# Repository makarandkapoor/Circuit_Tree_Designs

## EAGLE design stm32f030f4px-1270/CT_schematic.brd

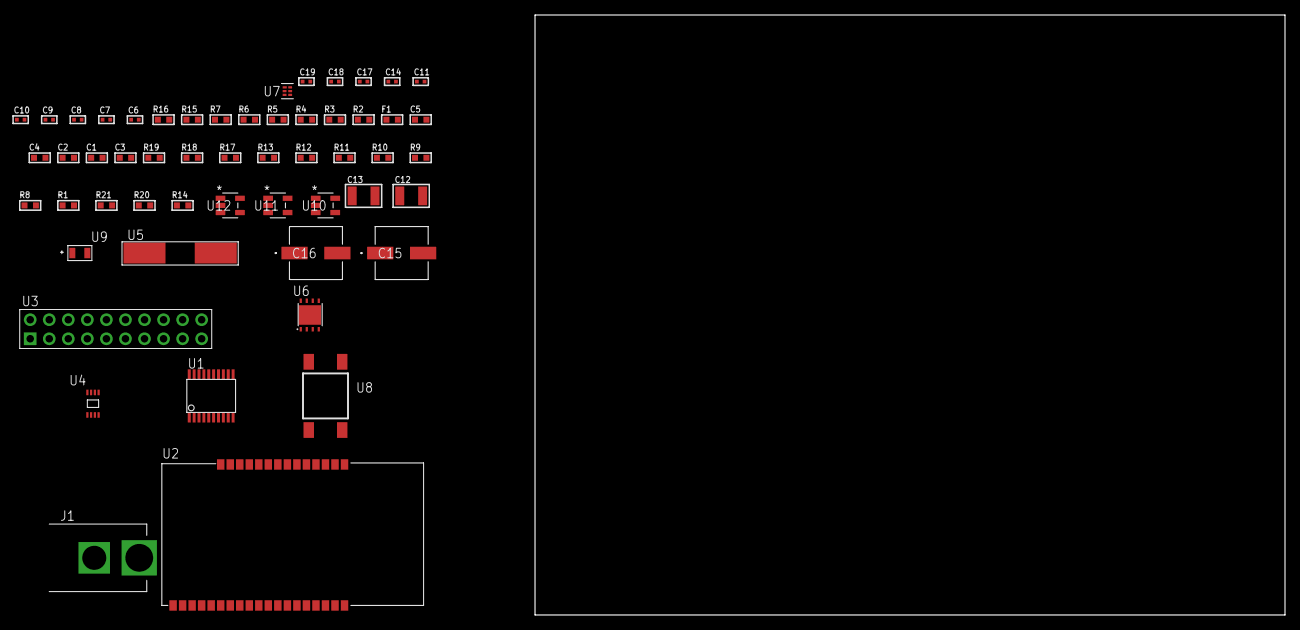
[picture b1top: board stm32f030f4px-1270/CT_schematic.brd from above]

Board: 2 copper layers, 100.0 x 80.0 mm, 54 parts (0 on the bottom side), 31 nets, no tracks yet.

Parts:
C1, C2: 1e-07; C0603
C3: 4.7e-06; C0603
C4: 1e-08; C0603
C5: 1e-06; C0603
C6, C7: 1e-11; C0402
C8, C9, C14: 1e-07; C0402
C10, C11, C17, C18, C19: 1e-08; C0402
C12, C13: 1e-05; C1210
C15, C16: 0.0001; EXV-9H
F1: 240.0; L0603
J1: PJ-037B; PJ-037B_PACKAGE
R1, R8, R9, R10, R11, R12, R13, R17, R18: 10000.0; R0603
R2, R16: 1000.0; R0603
R3: 1270.0; R0603
R4, R5: 4700.0; R0603
R6, R7: 2200.0; R0603
R14: 100000.0; R0603
R15: 1500.0; R0603
R19: 18000.0; R0603
R20: 470000.0; R0603
R21: 120000.0; R0603
U1: STM32F030F4P6; TSSOP20-I
U2: ETRX3587
U3: TST-110-05-T-D-RA
U4: 24AA128T-I/MNY; TDFN-8/6MM
U5: ABLS-25.000MHZ-B2F-T
U6: LP3878SDX-ADJ/NOPB; WSON-8
U7: TPS3895ADRYR; SON-6
U8: 4-1437565-2; SW_4-1437565-2
U9: Q65110A2395; LGM67K-G1J2-24-Z
U10, U11, U12: nc7sz125m5x; NC7SZ125M5X

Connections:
CLK_CRYSTAL_U1_2: C6.1, U1.2, U5.1
CLK_CRYSTAL_U1_3: C7.1, U1.3, U5.2
GND: C1.2, C2.2, C3.2, C4.2, C5.2, C6.2, C7.2, C8.2, C9.2, C10.2, C11.2, C12.2, C13.2, C14.2, C15.2, C16.2, C17.2, C18.2, C19.2, J1.2, R2.2, R8.2, R9.2, R16.2, R19.2, R21.2, U1.15, U2.1, U2.13, U2.19, U2.20, U2.31, U2.33, U3.4, U3.6, U3.8, U3.10, U3.12, U3.14, U3.16, U3.18, U3.20, U4.4, U4.7, U6.3, U6.PAD, U7.2, U9.C, U10.2, U10.3, U11.1, U11.3, U12.1, U12.3
NET_U1_1: R8.1, U1.1
NET_U1_4: R5.1, U1.4, U12.4
NET_U1_5: C4.1, C5.1, F1.1, U1.5
NET_U1_13: R3.1, U1.13, U9.A
NET_U1_14: R1.1, U1.14, U8.3, U8.4
NET_U1_17: R6.1, U1.17, U4.6
NET_U1_18: R7.1, U1.18, U4.5
NET_U2_7: R4.1, U2.7, U11.4
NET_U2_21: R9.1, U2.21
NET_U4_1: R11.1, U4.1
NET_U4_2: R12.1, U4.2
NET_U4_3: R13.1, U4.3
NET_U6_1: C11.1, U6.1
NET_U6_6: R15.2, R16.1, U6.6
NET_U6_8: R14.1, U6.8
NET_U7_1: R18.1, R19.1, U7.1
NET_U7_3: R20.2, R21.1, U7.3
NET_U7_4: R17.1, U7.4, U10.4, U11.2, U12.2
NET_U8_1: R2.1, U8.1, U8.2
PROC_SYS_SWCLK: U1.20, U3.9
PROC_SYS_SWDIO: U1.19, U3.7
PROC_USART1_CTS: U1.6, U2.8
PROC_USART1_RTS: U1.7, U2.6
PROC_USART1_RX: U1.9, U2.17
PROC_USART1_TX: U1.8, U2.18
RST_OUT_U3_SRESET_B: R10.1, U3.15, U10.1
VCC_S1_16V0: C12.1, C15.1, C16.1, J1.1, R14.2, U6.4
VCC_TIER1_2V5: C1.1, C2.1, C3.1, C8.1, C9.1, C10.1, C13.1, C14.1, C17.1, C18.1, C19.1, F1.2, R1.2, R3.2, R4.2, R5.2, R6.2, R7.2, R10.2, R11.2, R12.2, R13.2, R15.1, R17.2, R18.2, R20.1, U1.16, U2.32, U3.1, U4.8, U6.5, U7.6, U10.5, U11.5, U12.5

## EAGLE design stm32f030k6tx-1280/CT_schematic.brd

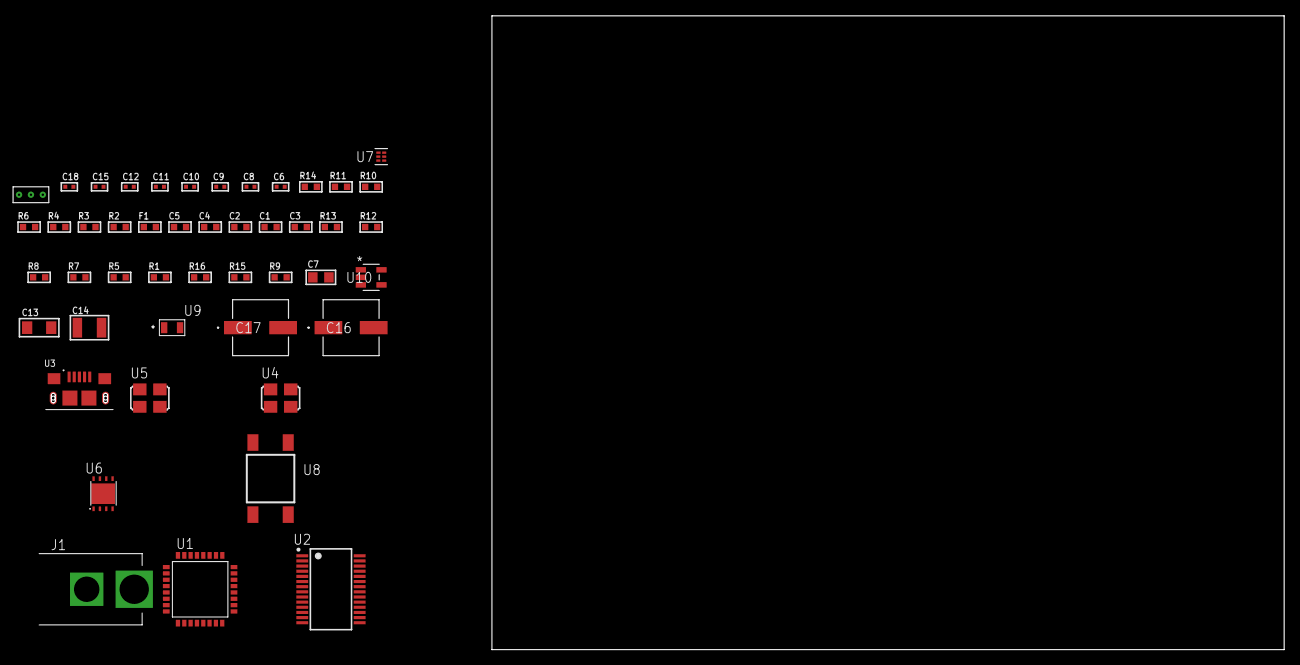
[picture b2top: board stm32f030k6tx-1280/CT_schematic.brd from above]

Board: 2 copper layers, 155.6 x 80.0 mm, 47 parts (0 on the bottom side), 29 nets, no tracks yet.

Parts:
C1, C2: 1e-07; C0603
C3: 4.7e-06; C0603
C4: 1e-08; C0603
C5: 1e-06; C0603
C6, C8, C9, C15: 1e-07; C0402
C7: 4.7e-06; C0805
C10, C11, C12, C18: 1e-08; C0402
C13: 1e-05; C1206
C14: 1e-05; C1210
C16, C17: 0.0001; EXV-9H
F1: 240.0; L0603
J1: PJ-037B; PJ-037B_PACKAGE
R1, R5, R7, R8, R12, R13: 10000.0; R0603
R2, R11: 1000.0; R0603
R3: 1600.5; R0603
R4, R6: 4700.0; R0603
R9: 100000.0; R0603
R10: 2231.0; R0603
R14: 9100.0; R0603
R15: 680000.0; R0603
R16: 120000.0; R0603
U1: STM32F030K6T6; LQFP32
U2: FT232RL-REEL; SSOP-28
U3: 10118193-0001LF; FCI_10118193-0001LF
U4: ASFL1-12MHZ-NCS; ASFL1
U5: ASFL1-25MHZ-NCS; ASFL1
U6: LP3878SDX-ADJ/NOPB; WSON-8
U7: TPS3895ADRYR; SON-6
U8: 4-1437565-2; SW_4-1437565-2
U9: Q65110A2395; LGM67K-G1J2-24-Z
U10: nc7sz125m5x; NC7SZ125M5X
U11: Dummy; DUMMY_PACKAGE_99

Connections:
CLK_U1_2: U1.2, U5.3
CLK_U2_27: U2.27, U4.3
GND: C1.2, C2.2, C3.2, C4.2, C5.2, C6.2, C7.2, C8.2, C9.2, C10.2, C11.2, C12.2, C13.2, C14.2, C15.2, C16.2, C17.2, C18.2, J1.2, R2.2, R5.2, R8.2, R11.2, R14.2, R16.2, U1.16, U1.32, U2.7, U2.18, U2.21, U2.25, U2.26, U3.5, U3.6, U3.7, U3.8, U3.9, U4.2, U5.2, U6.3, U6.PAD, U7.2, U9.C, U10.1, U10.3, U11.1
NET_U1_4: R4.1, U1.4, U10.4
NET_U1_5: C4.1, C5.1, F1.1, U1.5
NET_U1_29: R3.1, U1.29, U9.A
NET_U1_30: R1.1, U1.30, U8.3, U8.4
NET_U1_31: R5.1, U1.31
NET_U2_14: R7.1, U2.14
NET_U2_17: C8.1, U2.17
NET_U2_19: R8.1, U2.19
NET_U3_1: R6.1, U3.1
NET_U3_2: U2.16, U3.2
NET_U3_3: U2.15, U3.3
NET_U6_1: C12.1, U6.1
NET_U6_6: R10.2, R11.1, U6.6
NET_U6_8: R9.1, U6.8
NET_U7_1: R13.1, R14.1, U7.1
NET_U7_3: R15.2, R16.1, U7.3
NET_U7_4: R12.1, U7.4, U10.2
NET_U8_1: R2.1, U8.1, U8.2
PROC_TIM1_CH3N: U1.15, U11.3
PROC_TIM1_CH4: U1.21, U11.2
PROC_USART1_CTS: U1.6, U2.3
PROC_USART1_RTS: U1.7, U2.11
PROC_USART1_RX: U1.9, U2.1
PROC_USART1_TX: U1.8, U2.5
VCC_S1_6V0: C13.1, C16.1, C17.1, J1.1, R9.2, U6.4
VCC_TIER1_3V3: C1.1, C2.1, C3.1, C6.1, C7.1, C9.1, C10.1, C11.1, C14.1, C15.1, C18.1, F1.2, R1.2, R3.2, R4.2, R7.2, R10.1, R12.2, R13.2, R15.1, U1.1, U1.17, U2.4, U2.20, U4.4, U5.4, U6.5, U7.6, U10.5

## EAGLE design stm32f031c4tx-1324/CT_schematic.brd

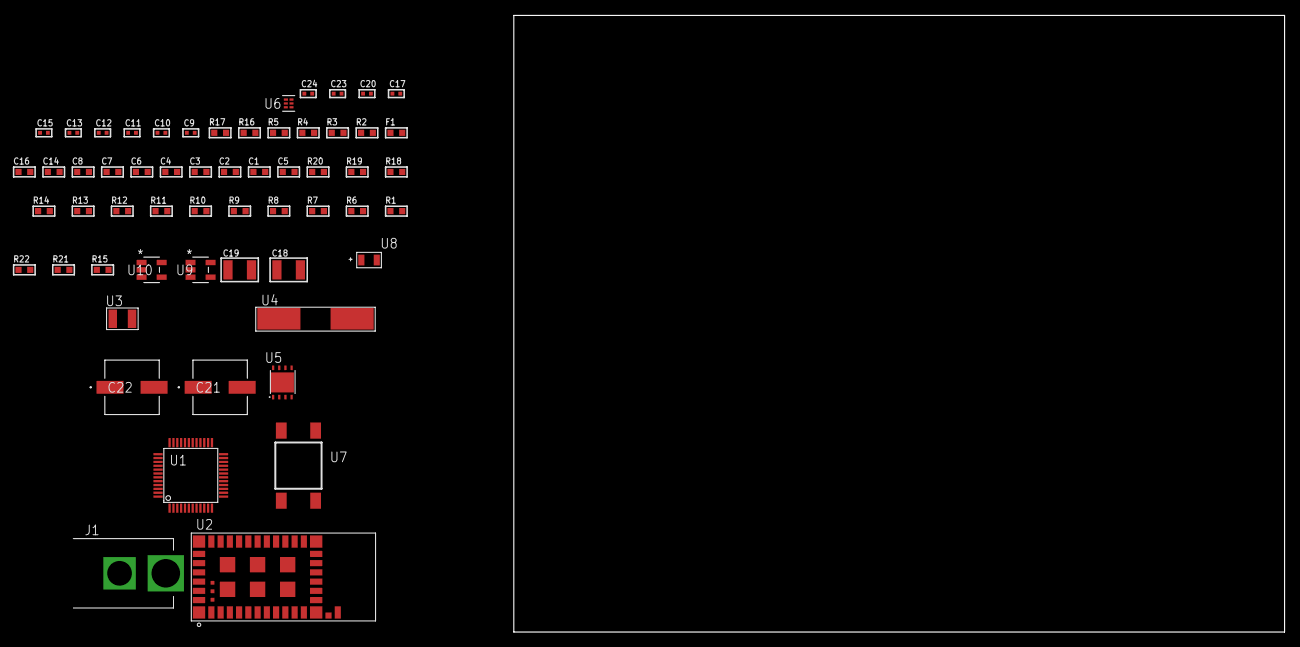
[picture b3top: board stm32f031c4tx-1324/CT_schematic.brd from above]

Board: 2 copper layers, 100.0 x 80.0 mm, 58 parts (0 on the bottom side), 28 nets, no tracks yet.

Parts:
C1, C8, C14, C16: 1e-06; C0603
C2, C3, C4, C6: 1e-07; C0603
C5: 4.7e-06; C0603
C7: 1e-08; C0603
C9, C10, C11, C12: 1e-11; C0402
C13, C15, C20: 1e-07; C0402
C17, C23, C24: 1e-08; C0402
C18, C19: 1e-05; C1210
C21, C22: 0.0001; EXV-9H
F1: 240.0; L0603
J1: PJ-037B; PJ-037B_PACKAGE
R1, R6, R7, R14, R18, R19: 10000.0; R0603
R2, R17: 1000.0; R0603
R3: 1500.0; R0603
R4, R5: 4700.0; R0603
R8, R9, R10, R11, R12, R13: 34000.0; R0603
R15: 100000.0; R0603
R16: 2000.0; R0603
R20: 11000.0; R0603
R21: 620000.0; R0603
R22: 120000.0; R0603
U1: stm32f031c4t7; LQFP48
U2: 88-00153-02
U3: ABS07-32.768KHZ-7-T
U4: ABLS-25.000MHZ-B2F-T
U5: LP3878SDX-ADJ/NOPB; WSON-8
U6: TPS3895ADRYR; SON-6
U7: 4-1437565-2; SW_4-1437565-2
U8: Q65110A2395; LGM67K-G1J2-24-Z
U9, U10: nc7sz125m5x; NC7SZ125M5X

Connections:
CLK_CRYSTAL_U1_3: C9.1, U1.3, U3.1
CLK_CRYSTAL_U1_4: C10.1, U1.4, U3.2
CLK_CRYSTAL_U1_5: C11.1, U1.5, U4.1
CLK_CRYSTAL_U1_6: C12.1, U1.6, U4.2
GND: C1.2, C2.2, C3.2, C4.2, C5.2, C6.2, C7.2, C8.2, C9.2, C10.2, C11.2, C12.2, C13.2, C14.2, C15.2, C16.2, C17.2, C18.2, C19.2, C20.2, C21.2, C22.2, C23.2, C24.2, J1.2, R2.2, R6.2, R17.2, R20.2, R22.2, U1.8, U1.23, U1.47, U2.1, U2.9, U2.13, U2.14, U2.15, U2.16, U2.17, U2.18, U2.19, U2.20, U2.21, U2.22, U2.23, U2.24, U2.25, U2.26, U2.27, U2.31, U2.32, U2.39, U2.40, U2.41, U2.42, U2.43, U2.44, U2.49, U5.3, U5.PAD, U6.2, U8.C, U9.1, U9.3, U10.1, U10.3
NET_U1_7: R5.1, U1.7, U10.4
NET_U1_9: C7.1, C8.1, F1.1, U1.9
NET_U1_44: R6.1, U1.44
NET_U1_45: R3.1, U1.45, U8.A
NET_U1_46: R1.1, U1.46, U7.3, U7.4
NET_U2_2: R10.1, U2.2
NET_U2_6: R14.1, U2.6
NET_U2_10: R4.1, U2.10, U9.4
NET_U2_11: R7.1, U2.11
NET_U2_34: R9.1, U2.34
NET_U5_1: C17.1, U5.1
NET_U5_6: R16.2, R17.1, U5.6
NET_U5_8: R15.1, U5.8
NET_U6_1: R19.1, R20.1, U6.1
NET_U6_3: R21.2, R22.1, U6.3
NET_U6_4: R18.1, U6.4, U9.2, U10.2
NET_U7_1: R2.1, U7.1, U7.2
PROC_SPI1_MISO: R8.1, U1.16, U2.35
PROC_SPI1_MOSI: R12.1, U1.17, U2.37
PROC_SPI1_NSS: R11.1, U1.14, U2.38
PROC_SPI1_SCK: R13.1, U1.15, U2.36
VCC_S1_11V3: C18.1, C21.1, C22.1, J1.1, R15.2, U5.4
VCC_TIER1_3V0: C1.1, C2.1, C3.1, C4.1, C5.1, C6.1, C13.1, C14.1, C15.1, C16.1, C19.1, C20.1, C23.1, C24.1, F1.2, R1.2, R3.2, R4.2, R5.2, R7.2, R8.2, R9.2, R10.2, R11.2, R12.2, R13.2, R14.2, R16.1, R18.2, R19.2, R21.1, U1.1, U1.24, U1.48, U2.12, U2.33, U5.5, U6.6, U9.5, U10.5

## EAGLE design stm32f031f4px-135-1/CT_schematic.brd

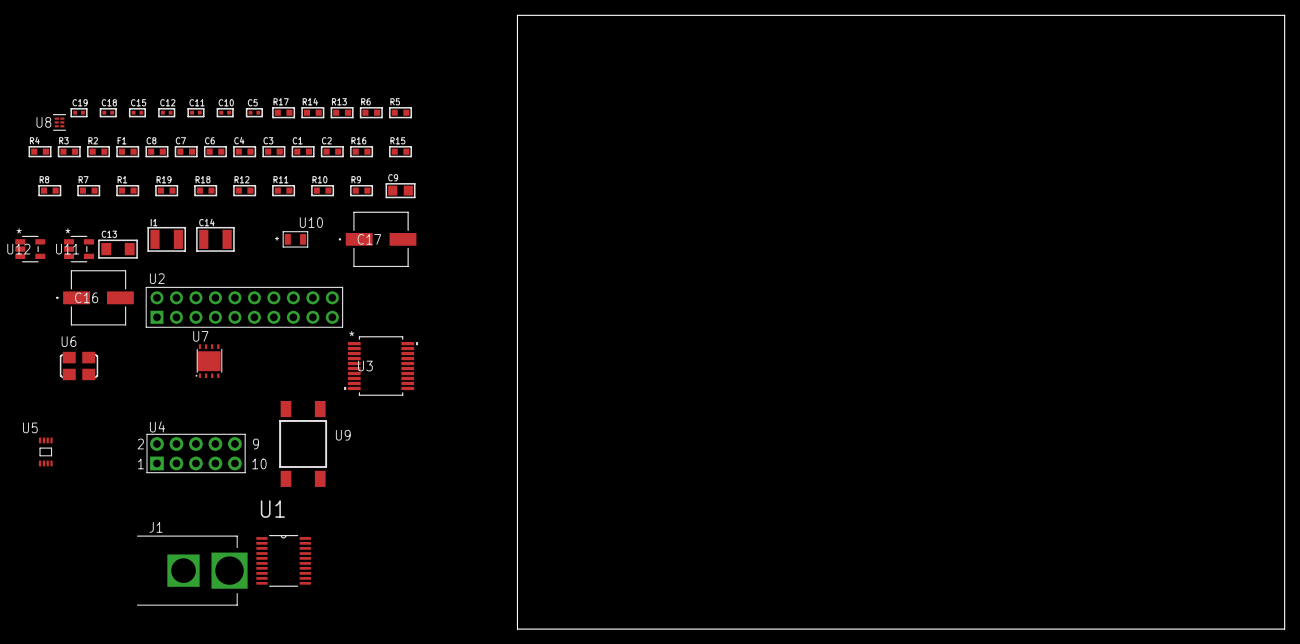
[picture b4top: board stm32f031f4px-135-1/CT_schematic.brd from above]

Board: 2 copper layers, 100.0 x 80.0 mm, 53 parts (0 on the bottom side), 37 nets, no tracks yet.

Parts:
C1: 1e-07; C0603
C2: 4.7e-06; C0603
C3: 1e-08; C0603
C4, C6, C7, C8: 1e-06; C0603
C5, C15: 1e-07; C0402
C9: 4.7e-06; C0805
C10, C11, C12, C18, C19: 1e-08; C0402
C13: 1e-05; C1206
C14: 1e-05; C1210
C16, C17: 0.0001; EXV-9H
F1: 240.0; L0603
I1: 1.5e-05; L1210
J1: PJ-037B; PJ-037B_PACKAGE
R1, R7, R8, R15, R16: 10000.0; R0603
R2, R14: 1000.0; R0603
R3: 1600.5; R0603
R4: 4700.0; R0603
R5, R6: 2200.0; R0603
R9, R10, R11, R12: 100000.0; R0603
R13: 2231.0; R0603
R17: 9100.0; R0603
R18: 680000.0; R0603
R19: 120000.0; R0603
U1: stm32f031f4p7; TSSOP20
U2: TST-110-05-T-D-RA
U3: MAX3218EAP+T; SSOP-20
U4: HTSS-105-01-G-D
U5: 24AA01T-I/MNY; TDFN-8/6MM
U6: ASFL1-25MHZ-NCS; ASFL1
U7: LP3878SDX-ADJ/NOPB; WSON-8
U8: TPS3895ADRYR; SON-6
U9: 4-1437565-2; SW_4-1437565-2
U10: Q65110A2395; LGM67K-G1J2-24-Z
U11, U12: nc7sz125m5x; NC7SZ125M5X

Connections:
CLK_U1_2: U1.2, U6.3
GND: C1.2, C2.2, C3.2, C4.2, C5.2, C6.2, C7.2, C8.2, C10.2, C11.2, C12.2, C13.2, C14.2, C15.2, C16.2, C17.2, C18.2, C19.2, J1.2, R2.2, R7.2, R14.2, R17.2, R19.2, U1.15, U2.4, U2.6, U2.8, U2.10, U2.12, U2.14, U2.16, U2.18, U2.20, U3.5, U3.17, U3.20, U4.9, U5.4, U6.2, U7.3, U7.PAD, U8.2, U10.C, U11.2, U11.3, U12.1, U12.3
NET_U1_1: R7.1, U1.1
NET_U1_4: R4.1, U1.4, U12.4
NET_U1_5: C3.1, C4.1, F1.1, U1.5
NET_U1_13: R3.1, U1.13, U10.A
NET_U1_14: R1.1, U1.14, U9.3, U9.4
NET_U1_17: R5.1, U1.17, U5.6
NET_U1_18: R6.1, U1.18, U5.5
NET_U3_1: I1.1, U3.1
NET_U3_2: R9.1, U3.2
NET_U3_3: R10.1, U3.3
NET_U3_4: R11.1, U3.4
NET_U3_15: C8.1, U3.15
NET_U3_16: C9.2, U3.16
NET_U3_18: C9.1, U3.18
NET_U3_19: C7.1, U3.19
NET_U4_3: U3.12, U4.3
NET_U4_4: U3.11, U4.4
NET_U4_5: U3.14, U4.5
NET_U4_6: U3.13, U4.6
NET_U7_1: C12.1, U7.1
NET_U7_6: R13.2, R14.1, U7.6
NET_U7_8: R12.1, U7.8
NET_U8_1: R16.1, R17.1, U8.1
NET_U8_3: R18.2, R19.1, U8.3
NET_U8_4: R15.1, U8.4, U11.4, U12.2
NET_U9_1: R2.1, U9.1, U9.2
PROC_SYS_SWCLK: U1.20, U2.9
PROC_SYS_SWDIO: U1.19, U2.7
PROC_USART1_CTS: U1.6, U3.8
PROC_USART1_RTS: U1.7, U3.10
PROC_USART1_RX: U1.9, U3.9
PROC_USART1_TX: U1.8, U3.7
RST_OUT_U2_SRESET_B: R8.1, U2.15, U11.1
VCC_S1_6V0: C13.1, C16.1, C17.1, J1.1, R12.2, U7.4
VCC_TIER1_3V3: C1.1, C2.1, C5.1, C6.1, C10.1, C11.1, C14.1, C15.1, C18.1, C19.1, F1.2, I1.2, R1.2, R3.2, R4.2, R5.2, R6.2, R8.2, R9.2, R10.2, R11.2, R13.1, R15.2, R16.2, R18.1, U1.16, U2.1, U3.6, U5.7, U5.8, U6.4, U7.5, U8.6, U11.5, U12.5

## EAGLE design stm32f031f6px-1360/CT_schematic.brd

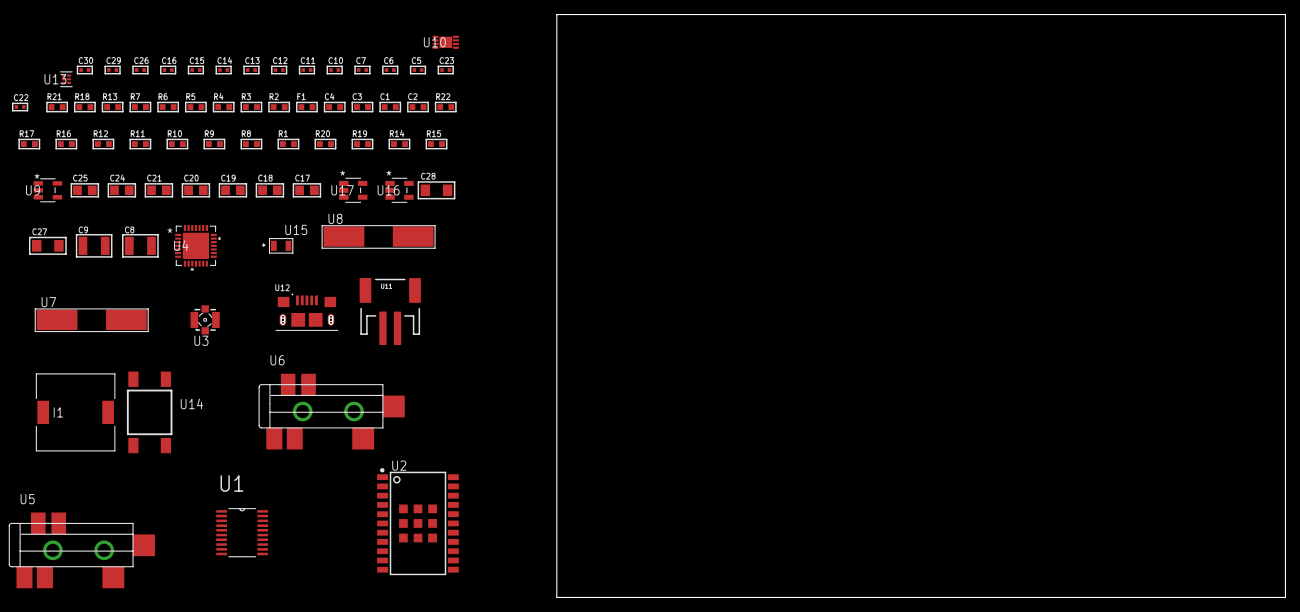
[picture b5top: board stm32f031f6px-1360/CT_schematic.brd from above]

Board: 2 copper layers, 71 parts (0 on the bottom side), 36 nets, no tracks yet.

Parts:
C1: 1e-07; C0603
C2: 4.7e-06; C0603
C3: 1e-08; C0603
C4: 1e-06; C0603
C5, C6: 1e-11; C0402
C7, C12, C13, C14, C15, C16, C26: 1e-07; C0402
C8, C9: 2.2e-05; C1210
C10, C11: 1e-09; C0402
C17, C18, C19, C20, C21, C24, C25: 1e-05; C0805
C22, C23: 2.2e-11; C0402
C27, C28: 1e-05; C1206
C29, C30: 1e-08; C0402
F1: 240.0; L0603
I1: 2.5e-06; DR1040
R1, R8, R9, R16, R17, R22: 10000.0; R0603
R2: 1000.0; R0603
R3: 1600.5; R0603
R4, R5: 4700.0; R0603
R6, R7: 2200.0; R0603
R10, R11, R12: 47000.0; R0603
R13: 680.0; R0603
R14: 220000.0; R0603
R15: 1000000.0; R0603
R18: 9100.0; R0603
R19: 680000.0; R0603
R20: 120000.0; R0603
R21: 2000.0; R0603
U1: stm32f031f6p7; TSSOP20
U2: A2200-A
U3: 73412-0114; COAXIAL_C
U4: WM8731CLSEFL; QFN-28
U5, U6: SJ-43515TS-SMT-TR
U7: ABLS-25.000MHZ-B2F-T
U8: ABLS-12.288MHZ-B4-T
U9: ltc3406es5; TSOT-23-5
U10: MCP73831T-2ACI/MC; DFN8_2X3MC
U11: S2B-PH-SM4-TB(LF)(SN); JST-2-SMD
U12: 10118193-0001LF; FCI_10118193-0001LF
U13: TPS3895ADRYR; SON-6
U14: 4-1437565-2; SW_4-1437565-2
U15: Q65110A2395; LGM67K-G1J2-24-Z
U16, U17: nc7sz125m5x; NC7SZ125M5X

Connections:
CLK_CRYSTAL_U1_2: C5.1, U1.2, U7.1
CLK_CRYSTAL_U1_3: C6.1, U1.3, U7.2
CLK_CRYSTAL_U4_1: C22.1, U4.1, U8.1
CLK_CRYSTAL_U4_2: C23.1, U4.2, U8.2
GND: C1.2, C2.2, C3.2, C4.2, C5.2, C6.2, C7.2, C11.2, C12.2, C13.2, C14.2, C15.2, C16.2, C17.2, C18.2, C19.2, C20.2, C21.2, C22.2, C23.2, C24.2, C25.1, C25.2, C26.2, C27.2, C28.2, C29.2, C30.2, R2.2, R8.2, R10.2, R11.2, R12.2, R14.2, R18.2, R20.2, R21.2, U1.15, U2.7, U2.8, U2.23, U2.24, U2.25, U2.26, U2.27, U2.28, U2.29, U2.30, U2.31, U4.4, U4.15, U4.19, U4.25, U4.26, U4.29, U5.1, U6.1, U9.2, U10.6, U10.9, U11.2, U12.5, U12.6, U12.7, U12.8, U12.9, U13.2, U15.C, U16.1, U16.3, U17.1, U17.3
INPUT_USBPOWER_5V: C27.1, R22.2, U10.1, U10.2, U12.1
NET_U1_1: R8.1, U1.1
NET_U1_4: R5.1, U1.4, U17.4
NET_U1_5: C3.1, C4.1, F1.1, U1.5
NET_U1_17: R6.1, U1.17, U2.15
NET_U1_18: R7.1, U1.18, U2.16
NET_U1_19: R3.1, U1.19, U15.A
NET_U1_20: R1.1, U1.20, U14.3, U14.4
NET_U2_2: R9.2, U2.2
NET_U2_17: R9.1, U2.17
NET_U2_22: R4.1, U2.22, U16.4
NET_U3_1: U2.11, U3.1
NET_U3_2: U2.10, U3.2, U3.3, U3.4
NET_U4_20: C16.1, C21.1, U4.20
NET_U5_2: C9.1, R11.1, U5.2
NET_U5_5: C8.1, R10.1, U5.5
NET_U6_5: C10.1, C11.1, R12.1, R13.1, U6.5
NET_U9_3: I1.1, U9.3
NET_U9_5: R14.1, R15.1, U9.5
NET_U9_ATNET_3: I1.2, R15.2
NET_U10_5: R22.1, U10.5
NET_U10_8: R21.1, U10.8
NET_U13_1: R17.1, R18.1, U13.1
NET_U13_3: R19.2, R20.1, U13.3
NET_U13_4: R16.1, U13.4, U16.2, U17.2
NET_U14_1: R2.1, U14.1, U14.2
PROC_I2S1_CK: U1.11, U4.7
PROC_I2S1_SD: U1.13, U4.8
PROC_I2S1_WS: U1.10, U4.9, U4.11
VCC_S1_3V7: C24.1, C28.1, U9.4, U10.3, U10.4, U11.1
VCC_TIER1_3V3: C1.1, C2.1, C7.1, C12.1, C13.1, C14.1, C15.1, C17.1, C18.1, C19.1, C20.1, C25.2, C26.1, C29.1, C30.1, F1.2, I1.2, R1.2, R3.2, R4.2, R5.2, R6.2, R7.2, R15.2, R16.2, R17.2, R19.1, U1.16, U2.20, U4.3, U4.5, U4.12, U4.18, U13.6, U16.5, U17.5

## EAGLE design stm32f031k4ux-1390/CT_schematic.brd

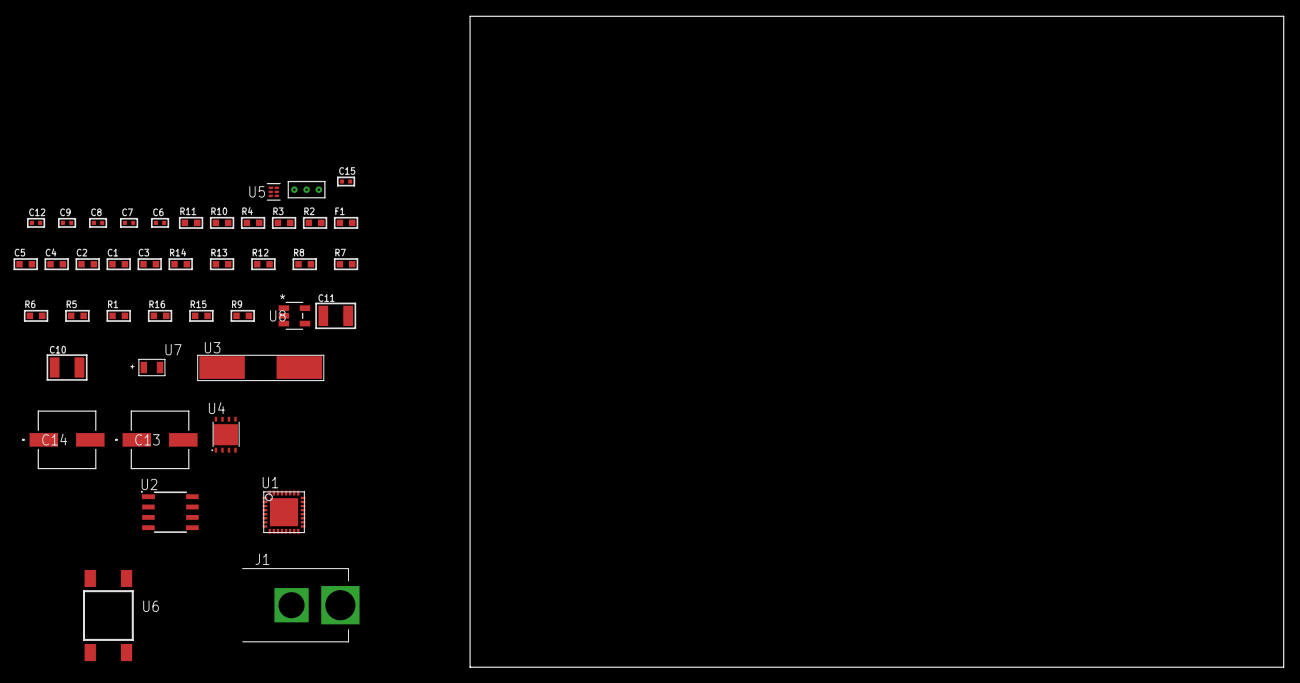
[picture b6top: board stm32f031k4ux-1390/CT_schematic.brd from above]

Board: 2 copper layers, 100.0 x 80.0 mm, 42 parts (0 on the bottom side), 25 nets, no tracks yet.

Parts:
C1, C2: 1e-07; C0603
C3: 4.7e-06; C0603
C4: 1e-08; C0603
C5: 1e-06; C0603
C6, C7: 1e-11; C0402
C8, C9, C15: 1e-08; C0402
C10, C11: 1e-05; C1210
C12: 1e-07; C0402
C13, C14: 0.0001; EXV-9H
F1: 240.0; L0603
J1: PJ-037B; PJ-037B_PACKAGE
R1, R5, R6, R7, R8, R12, R13: 10000.0; R0603
R2, R11: 1000.0; R0603
R3: 1270.0; R0603
R4: 4700.0; R0603
R9: 100000.0; R0603
R10: 1500.0; R0603
R14: 18000.0; R0603
R15: 470000.0; R0603
R16: 120000.0; R0603
U1: stm32f031k4u7; UFQFPN32
U2: AT25512N-SH-T; SOIC-8
U3: ABLS-25.000MHZ-B2F-T
U4: LP3878SDX-ADJ/NOPB; WSON-8
U5: TPS3895ADRYR; SON-6
U6: 4-1437565-2; SW_4-1437565-2
U7: Q65110A2395; LGM67K-G1J2-24-Z
U8: nc7sz125m5x; NC7SZ125M5X
U9: Dummy; DUMMY_PACKAGE_85

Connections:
CLK_CRYSTAL_U1_2: C6.1, U1.2, U3.1
CLK_CRYSTAL_U1_3: C7.1, U1.3, U3.2
GND: C1.2, C2.2, C3.2, C4.2, C5.2, C6.2, C7.2, C8.2, C9.2, C10.2, C11.2, C12.2, C13.2, C14.2, C15.2, J1.2, R2.2, R5.2, R11.2, R14.2, R16.2, U1.EPAD, U2.4, U4.3, U4.PAD, U5.2, U7.C, U8.1, U8.3, U9.1
NET_U1_4: R4.1, U1.4, U8.4
NET_U1_5: C4.1, C5.1, F1.1, U1.5
NET_U1_30: R3.1, U1.30, U7.A
NET_U1_31: R5.1, U1.31
NET_U1_32: R1.1, U1.32, U6.3, U6.4
NET_U2_3: R6.1, U2.3
NET_U2_7: R8.1, U2.7
NET_U4_1: C9.1, U4.1
NET_U4_6: R10.2, R11.1, U4.6
NET_U4_8: R9.1, U4.8
NET_U5_1: R13.1, R14.1, U5.1
NET_U5_3: R15.2, R16.1, U5.3
NET_U5_4: R12.1, U5.4, U8.2
NET_U6_1: R2.1, U6.1, U6.2
PROC_ADC_IN1: U1.7, U9.3
PROC_ADC_IN9: U1.15, U9.2
PROC_SPI1_MISO: U1.12, U2.2
PROC_SPI1_MOSI: U1.13, U2.5
PROC_SPI1_NSS: R7.1, U1.10, U2.1
PROC_SPI1_SCK: U1.11, U2.6
VCC_S1_15V0: C10.1, C13.1, C14.1, J1.1, R9.2, U4.4
VCC_TIER1_2V5: C1.1, C2.1, C3.1, C8.1, C11.1, C12.1, C15.1, F1.2, R1.2, R3.2, R4.2, R6.2, R7.2, R8.2, R10.1, R12.2, R13.2, R15.1, U1.1, U1.17, U2.8, U4.5, U5.6, U8.5

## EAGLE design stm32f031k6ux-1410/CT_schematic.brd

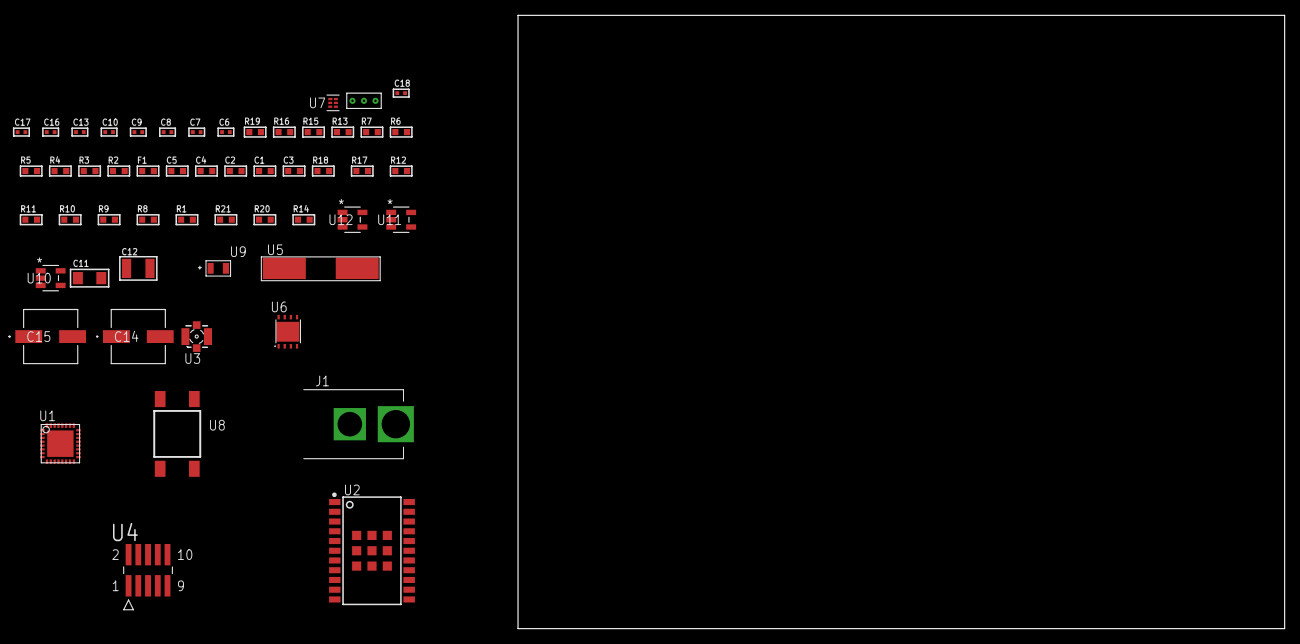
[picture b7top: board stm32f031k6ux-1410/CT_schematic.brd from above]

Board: 2 copper layers, 100.0 x 80.0 mm, 54 parts (0 on the bottom side), 30 nets, no tracks yet.

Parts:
C1, C2: 1e-07; C0603
C3: 4.7e-06; C0603
C4: 1e-08; C0603
C5: 1e-06; C0603
C6, C7: 1e-11; C0402
C8, C9, C13: 1e-07; C0402
C10, C16, C17, C18: 1e-08; C0402
C11: 1e-05; C1206
C12: 1e-05; C1210
C14, C15: 0.0001; EXV-9H
F1: 240.0; L0603
J1: PJ-037B; PJ-037B_PACKAGE
R1, R8, R9, R10, R11, R12, R17, R18: 10000.0; R0603
R2, R16: 1000.0; R0603
R3: 1600.5; R0603
R4, R5: 4700.0; R0603
R6, R7: 2200.0; R0603
R13: 5.0; R0603
R14: 100000.0; R0603
R15: 2231.0; R0603
R19: 9100.0; R0603
R20: 680000.0; R0603
R21: 120000.0; R0603
U1: stm32f031k6u7; UFQFPN32
U2: A2200-A
U3: 73412-0114; COAXIAL_C
U4: FTSH-105-01-L-DV-K; SAMTEC_FTSH-105-01-L-DV-K
U5: ABLS-25.000MHZ-B2F-T
U6: LP3878SDX-ADJ/NOPB; WSON-8
U7: TPS3895ADRYR; SON-6
U8: 4-1437565-2; SW_4-1437565-2
U9: Q65110A2395; LGM67K-G1J2-24-Z
U10, U11, U12: nc7sz125m5x; NC7SZ125M5X
U13: Dummy; DUMMY_PACKAGE_111

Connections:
CLK_CRYSTAL_U1_2: C6.1, U1.2, U5.1
CLK_CRYSTAL_U1_3: C7.1, U1.3, U5.2
GND: C1.2, C2.2, C3.2, C4.2, C5.2, C6.2, C7.2, C8.2, C9.2, C10.2, C11.2, C12.2, C13.2, C14.2, C15.2, C16.2, C17.2, C18.2, J1.2, R2.2, R8.2, R13.2, R16.2, R19.2, R21.2, U1.EPAD, U2.7, U2.8, U2.23, U2.24, U2.25, U2.26, U2.27, U2.28, U2.29, U2.30, U2.31, U4.3, U4.5, U6.3, U6.PAD, U7.2, U9.C, U10.2, U10.3, U11.1, U11.3, U12.1, U12.3, U13.1
NET_U1_4: R5.1, U1.4, U12.4
NET_U1_5: C4.1, C5.1, F1.1, U1.5
NET_U1_19: R6.1, U1.19, U2.15
NET_U1_20: R7.1, U1.20, U2.16
NET_U1_30: R3.1, U1.30, U9.A
NET_U1_31: R8.1, U1.31
NET_U1_32: R1.1, U1.32, U8.3, U8.4
NET_U2_2: R9.2, U2.2
NET_U2_17: R9.1, U2.17
NET_U2_22: R4.1, U2.22, U11.4
NET_U3_1: U2.11, U3.1
NET_U3_2: U2.10, U3.2, U3.3, U3.4
NET_U4_9: R13.1, U4.9
NET_U6_1: C10.1, U6.1
NET_U6_6: R15.2, R16.1, U6.6
NET_U6_8: R14.1, U6.8
NET_U7_1: R18.1, R19.1, U7.1
NET_U7_3: R20.2, R21.1, U7.3
NET_U7_4: R17.1, U7.4, U10.4, U11.2, U12.2
NET_U8_1: R2.1, U8.1, U8.2
PROC_SYS_SWCLK: R11.1, U1.24, U4.4
PROC_SYS_SWDIO: R12.1, U1.23, U4.2
PROC_TIM1_CH3N: U1.15, U13.3
PROC_TIM1_CH4: U1.21, U13.2
RST_OUT_U4_JTAG_RST_B: R10.1, U4.10, U10.1
VCC_S1_10V8: C11.1, C14.1, C15.1, J1.1, R14.2, U6.4
VCC_TIER1_3V3: C1.1, C2.1, C3.1, C8.1, C9.1, C12.1, C13.1, C16.1, C17.1, C18.1, F1.2, R1.2, R3.2, R4.2, R5.2, R6.2, R7.2, R10.2, R11.2, R12.2, R15.1, R17.2, R18.2, R20.1, U1.1, U1.17, U2.20, U4.1, U6.5, U7.6, U10.5, U11.5, U12.5

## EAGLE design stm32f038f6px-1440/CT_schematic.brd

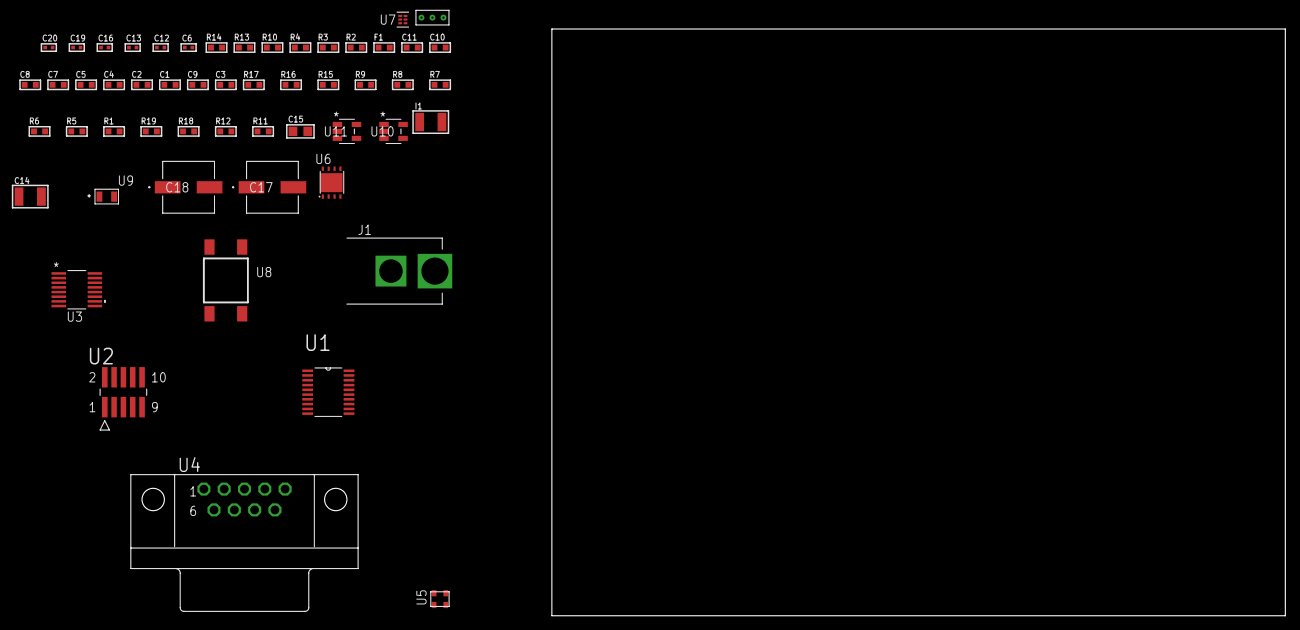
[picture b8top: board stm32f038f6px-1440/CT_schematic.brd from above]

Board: 2 copper layers, 100.0 x 80.0 mm, 54 parts (0 on the bottom side), 36 nets, no tracks yet.

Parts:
C1, C2: 1e-07; C0603
C3: 4.7e-06; C0603
C4: 1e-08; C0603
C5, C7, C8, C10, C11: 1e-06; C0603
C6, C16: 1e-07; C0402
C9: 2.2e-07; C0603
C12, C13, C19, C20: 1e-08; C0402
C14: 1e-05; C1210
C15: 1e-05; C0805
C17, C18: 0.0001; EXV-9H
F1: 240.0; L0603
I1: 1e-05; L1210
J1: PJ-037B; PJ-037B_PACKAGE
R1, R5, R6, R7, R8, R9, R15, R16: 10000.0; R0603
R2, R14: 1000.0; R0603
R3: 910.0; R0603
R4: 4700.0; R0603
R10: 5.0; R0603
R11, R12: 100000.0; R0603
R13: 806.0; R0603
R17: 82000.0; R0603
R18: 300000.0; R0603
R19: 120000.0; R0603
U1: stm32f038f6p6; TSSOP20
U2: FTSH-105-01-L-DV-K; SAMTEC_FTSH-105-01-L-DV-K
U3: LTC2804CGN-1#PBF; SSOP-16
U4: 182-009-113R531; 182-009-MALE
U5: ASDMB-25.000MHZ-EC-T; ASDMB-XX.XXXXMHZ-XX-XX-XXX
U6: LP3878SDX-ADJ/NOPB; WSON-8
U7: TPS3895ADRYR; SON-6
U8: 4-1437565-2; SW_4-1437565-2
U9: Q65110A2395; LGM67K-G1J2-24-Z
U10, U11: nc7sz125m5x; NC7SZ125M5X
U12: Dummy; DUMMY_PACKAGE_113

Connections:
CLK_U1_2: U1.2, U5.3
GND: C1.2, C2.2, C3.2, C4.2, C5.2, C6.2, C7.2, C8.2, C10.2, C11.2, C12.2, C13.2, C14.2, C15.2, C16.2, C17.2, C18.2, C19.2, C20.2, J1.2, R2.2, R5.2, R6.2, R10.2, R14.2, R17.2, R19.2, U1.15, U2.3, U2.5, U3.8, U4.5, U5.2, U6.3, U6.PAD, U7.2, U9.C, U10.2, U10.3, U11.1, U11.3, U12.1
NET_U1_1: R5.1, U1.1
NET_U1_4: R4.1, U1.4, U11.4
NET_U1_5: C4.1, C5.1, F1.1, U1.5
NET_U1_14: R6.1, U1.14
NET_U1_17: R3.1, U1.17, U9.A
NET_U1_18: R1.1, U1.18, U8.3, U8.4
NET_U2_9: R10.1, U2.9
NET_U3_6: C7.1, U3.6
NET_U3_7: C9.1, I1.2, U3.7
NET_U3_9: C8.1, U3.9
NET_U3_10: C9.2, U3.10
NET_U3_11: R11.1, U3.11
NET_U4_2: U3.1, U4.2
NET_U4_3: U3.3, U4.3
NET_U4_7: U3.2, U4.7
NET_U4_8: U3.4, U4.8
NET_U6_1: C13.1, U6.1
NET_U6_6: R13.2, R14.1, U6.6
NET_U6_8: R12.1, U6.8
NET_U7_1: R16.1, R17.1, U7.1
NET_U7_3: R18.2, R19.1, U7.3
NET_U7_4: R15.1, U7.4, U10.4, U11.2
NET_U8_1: R2.1, U8.1, U8.2
PROC_SYS_SWCLK: R8.1, U1.20, U2.4
PROC_SYS_SWDIO: R9.1, U1.19, U2.2
PROC_TIM1_CH1N: U1.13, U12.2
PROC_TIM14_CH1: U1.10, U12.3
PROC_USART1_CTS: U1.6, U3.13
PROC_USART1_RTS: U1.7, U3.15
PROC_USART1_RX: U1.9, U3.16
PROC_USART1_TX: U1.8, U3.14
RST_OUT_U2_JTAG_RST_B: R7.1, U2.10, U10.1
VCC_S1_15V5: C14.1, C17.1, C18.1, J1.1, R12.2, U6.4
VCC_TIER1_1V8: C1.1, C2.1, C3.1, C6.1, C10.1, C11.1, C12.1, C15.1, C16.1, C19.1, C20.1, F1.2, I1.1, R1.2, R3.2, R4.2, R7.2, R8.2, R9.2, R11.2, R13.1, R15.2, R16.2, R18.1, U1.16, U2.1, U3.5, U3.12, U5.4, U6.5, U7.6, U10.5, U11.5

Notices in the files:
parts and their libraries:
circuit_tree: (C) 2014 Tomasz Boleslaw CEDRO, cederom@tlen.pl, http://www.tomek.cedro.info.
